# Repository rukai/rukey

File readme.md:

# Rukey

## About

This was designed quickly as my personal keyboard, I would like to make this a properly documented project that others can build but don't have the capacity at the moment.

I used the sofle pico as a base but changed pretty much everything in order to recreate the moonlander but with the goal of being a budget build.

## BOM

[Printed parts onshape](https://cad.onshape.com/documents/f6585266405bfc96ac0755a6/w/eb9972e583e4bd12c4cf19cb/e/e24845aae63ec51d7ef00fa9?renderMode=0&uiState=69eeedeaa3d4f3ef21615389)

|Quantity|Item|Note|
|-|-|-|
|74| MX compatible switches| |
|74| MX compatible kailh hotswap sockets| |
|74| Surface mount SOD-123 1N4148 diodes| |
|2| 2x08 2.00mm IDC straight socket| |
|1| 2x08 2.00mm IDC cable - at least 20cm long| |
|4| 2x03 2.00mm pin header |used as IDC socket in tight area |
|2| 2x03 2.00mm IDC cable - ~10cm long | |
|1| printed left base|print with supports for the bridge, can be done with auto supports configured to 1 degree|
|1| printed right base| same as above|
|1| printed switch plate - left main|no supports|
|1| printed switch plate - right main|no supports|
|1| printed switch plate - left thumb cluster|no supports|
|1| printed switch plate - right thumb cluster|no supports|
|2| printed washers|no supports|
|4| m3 machine screws - 25mm long||
|2| m3 machine screws - 20mm long||
|2| m3 machine screws - 14mm long||
|2| m3 machine screws - 12mm long||
|10| m3 square nuts| |
|2|main PCB| |
|2|thumb cluster PCB| |

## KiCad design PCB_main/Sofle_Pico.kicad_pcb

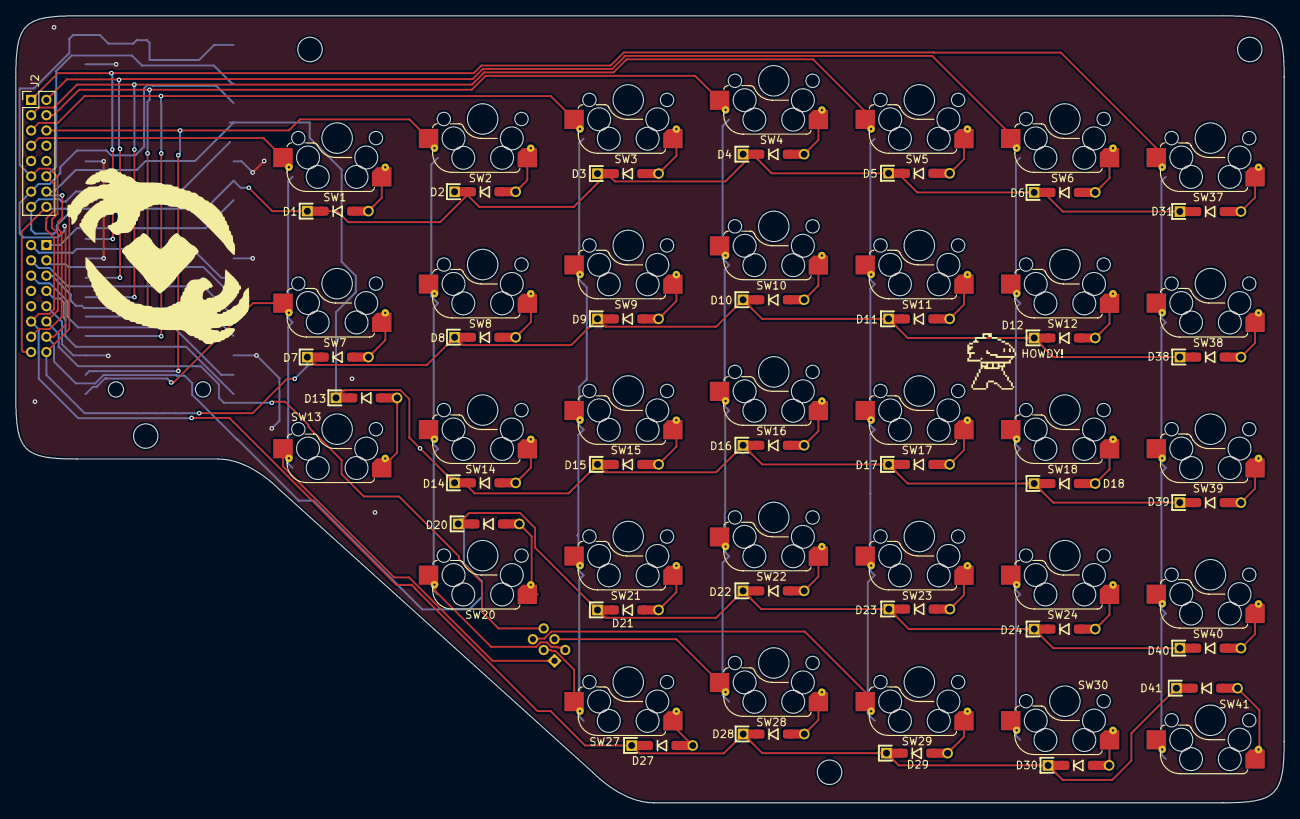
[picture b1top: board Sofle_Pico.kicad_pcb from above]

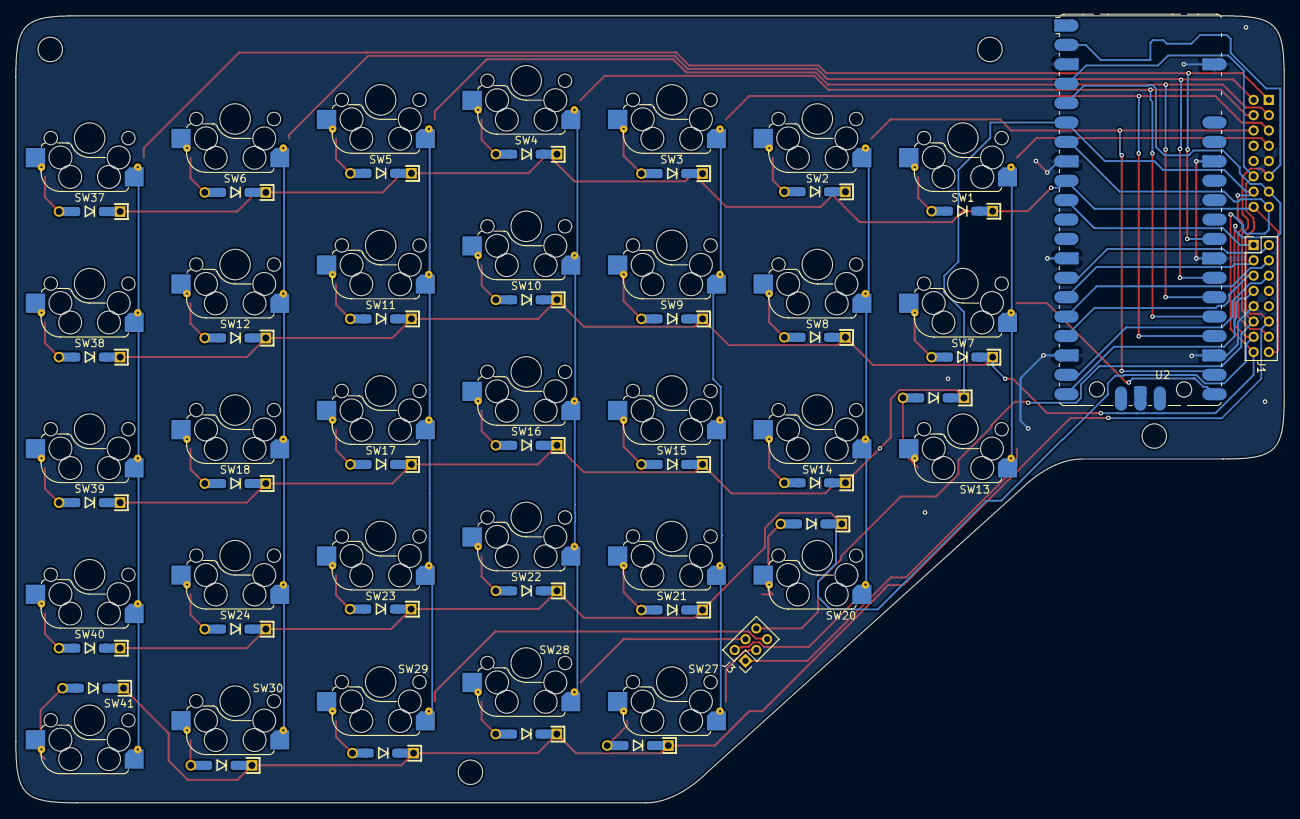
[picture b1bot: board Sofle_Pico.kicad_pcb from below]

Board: 2 copper layers, 166.0 x 103.0 mm, 68 parts (67 on the bottom side), 53 nets.

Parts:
D1, D2, D3, D4, D5, D6, D7, D8, D9, D10, D11, D12, D13, D14, D15, D16, D17, D18, D20, D21, D22, D23, D24, D27, D28, D29, D30, D31, D38, D39, D40, D41: D; D_SOD-123_DO-35_Hybrid_DoubleSided_V2
J1, J2: Conn_02x08_Top_Bottom; PinHeader_2x08_P2.00mm_Vertical
J3: Conn_02x03; PinHeader_2x03_P2.00mm_Vertical
SW1, SW2, SW3, SW4, SW5, SW6, SW7, SW8, SW9, SW10, SW11, SW12, SW13, SW14, SW15, SW16, SW17, SW18, SW20, SW21, SW22, SW23, SW24, SW27, SW28, SW29, SW30, SW37, SW38, SW39, SW40, SW41: SW_PUSH; Cherry_MX_DS_Hotswap_v3.5.4
U2: Pico; RaspberryPi_Pico_SMD

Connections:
GND: J1.9, J2.9, U2.3 (GND), U2.8 (GND), U2.13 (GND), U2.18 (GND), U2.23 (GND), U2.28 (GND), U2.33 (AGND), U2.38 (GND)
unnamed: D1.2 (A), SW1.2
unnamed: D2.2 (A), SW2.2
unnamed: D3.2 (A), SW3.2
unnamed: D4.2 (A), SW4.2
unnamed: D5.2 (A), SW5.2
unnamed: D6.2 (A), SW6.2
unnamed: D7.2 (A), SW7.2
unnamed: D8.2 (A), SW8.2
unnamed: D9.2 (A), SW9.2
unnamed: D10.2 (A), SW10.2
unnamed: D11.2 (A), SW11.2
unnamed: D12.2 (A), SW12.2
unnamed: D13.2 (A), SW13.2
unnamed: D14.2 (A), SW14.2
unnamed: D15.2 (A), SW15.2
unnamed: D16.2 (A), SW16.2
unnamed: D17.2 (A), SW17.2
unnamed: D18.2 (A), SW18.2
unnamed: D20.2 (A), SW20.2
unnamed: D21.2 (A), SW21.2
unnamed: D22.2 (A), SW22.2
unnamed: D23.2 (A), SW23.2
unnamed: D24.2 (A), SW24.2
unnamed: D27.2 (A), SW27.2
unnamed: D28.2 (A), SW28.2
unnamed: D29.2 (A), SW29.2
unnamed: D30.2 (A), SW30.2
unnamed: D31.2 (A), SW37.2
unnamed: D38.2 (A), SW38.2
unnamed: D39.2 (A), SW39.2
unnamed: D40.2 (A), SW40.2
unnamed: D41.2 (A), SW41.2
lcol0: J2.7, J3.1, SW1.1, SW7.1, SW13.1, U2.21 (GPIO16)
lcol1: J2.6, J3.2, SW2.1, SW8.1, SW14.1, SW20.1, U2.22 (GPIO17)
lcol2: J2.5, J3.3, SW3.1, SW9.1, SW15.1, SW21.1, SW27.1, U2.24 (GPIO18)
lcol3: J2.4, J3.4, SW4.1, SW10.1, SW16.1, SW22.1, SW28.1, U2.25 (GPIO19)
lcol4: J2.3, J3.5, SW5.1, SW11.1, SW17.1, SW23.1, SW29.1, U2.26 (GPIO20)
lcol5: J2.2, SW6.1, SW12.1, SW18.1, SW24.1, SW30.1, U2.27 (GPIO21)
lcol6: J2.1, SW37.1, SW38.1, SW39.1, SW40.1, SW41.1, U2.29 (GPIO22)
rcol0: J1.7, U2.20 (GPIO15)
rcol1: J1.6, U2.19 (GPIO14)
rcol2: J1.5, U2.17 (GPIO13)
rcol3: J1.4, U2.16 (GPIO12)
rcol4: J1.3, U2.15 (GPIO11)
rcol5: J1.2, U2.14 (GPIO10)
rcol6: J1.1, U2.10 (GPIO7)
row0: D1.1 (K), D2.1 (K), D3.1 (K), D4.1 (K), D5.1 (K), D6.1 (K), D31.1 (K), J1.16, J2.16, U2.9 (GPIO6)
row1: D7.1 (K), D8.1 (K), D9.1 (K), D10.1 (K), D11.1 (K), D12.1 (K), D38.1 (K), J1.15, J2.15, U2.7 (GPIO5)
row2: D13.1 (K), D14.1 (K), D15.1 (K), D16.1 (K), D17.1 (K), D18.1 (K), D39.1 (K), J1.14, J2.14, U2.6 (GPIO4)
row3: D20.1 (K), D21.1 (K), D22.1 (K), D23.1 (K), D24.1 (K), D40.1 (K), J1.13, J2.13, U2.5 (GPIO3)
row4: D27.1 (K), D28.1 (K), D29.1 (K), D30.1 (K), D41.1 (K), J1.12, J2.12, U2.4 (GPIO2)
row5: J1.11, J2.11, J3.6, U2.2 (GPIO1)

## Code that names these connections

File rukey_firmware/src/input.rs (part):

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        let col12_pin = 10; // rcol 5
        let col13_pin = 7; // rcol 6

        let row0_pin = 6;
        let row1_pin = 5;
        let row2_pin = 4;
        let row3_pin = 3;
        let row4_pin = 2;
        let row5_pin = 1;

        // Load initial config
        let _meta = self.config_flash.lock().await.load_meta().await; // TODO: pin remappings
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            output(self.pins[col13_pin].take().unwrap()),
        ];
        let rows = [
            input(self.pins[row0_pin].take().unwrap()),
            input(self.pins[row1_pin].take().unwrap()),
            input(self.pins[row2_pin].take().unwrap()),
            input(self.pins[row3_pin].take().unwrap()),
            input(self.pins[row4_pin].take().unwrap()),
            input(self.pins[row5_pin].take().unwrap()),
        ];

        let mut state = State::new();
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
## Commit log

2026-04-09 second board is not smart
2026-04-11 chop off unneeded keys
2026-04-11 remove junk
2026-04-11 add thumb cluster board
2026-04-11 improve positioning
2026-04-25 more pcb progress
2026-04-25 more
2026-04-25 rotate idc socket
2026-04-25 route thumb cluster
2026-04-25 add export script
2026-04-26 adjust holes
2026-04-26 more pcb
2026-04-26 relayout thumbcluster
2026-04-27 thumb cluster connection uses idc
2026-05-05 add firmware
2026-05-08 document issues
2026-05-09 fix pcb
2026-05-09 more pcb work
2026-05-16 implement matrix query in firmware
2026-05-16 improve pin mapping
2026-05-20 remove pico testpads from pcb
2026-06-02 fix key mapping
2026-06-06 bom fix
2026-06-07 full mapping
2026-06-07 review
2026-06-07 better integrate with mapping state machines
2026-06-07 split left-right
2026-06-08 thumb cluster
2026-06-08 maybe
2026-06-08 Merge pull request #2 from rukai/improve-mapping-naming
    Improve mapping naming
